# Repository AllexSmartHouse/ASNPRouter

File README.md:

# ASNPRouter
Allex Serial Network Protocol router device based on stm32 board(blue pill) and arduino libs(STM32GENERIC)

# Hardware  
STM32 board - blue pill(or another with simillar pinout)  

DC-DC converter(default PCB based on LM2596)

PCB designed to use with cheap plastic case:  

# Software  
Arduino Libs:  
https://github.com/AllexSmartHouse/STM32GENERIC  

Use ST-Link  
Settings:  
Board: Blue pill  
USB: Disabled, No usb  
Serial communication: SerialUART1  
JTAG/SWD debugging: SWD
Upload method: ST-Link

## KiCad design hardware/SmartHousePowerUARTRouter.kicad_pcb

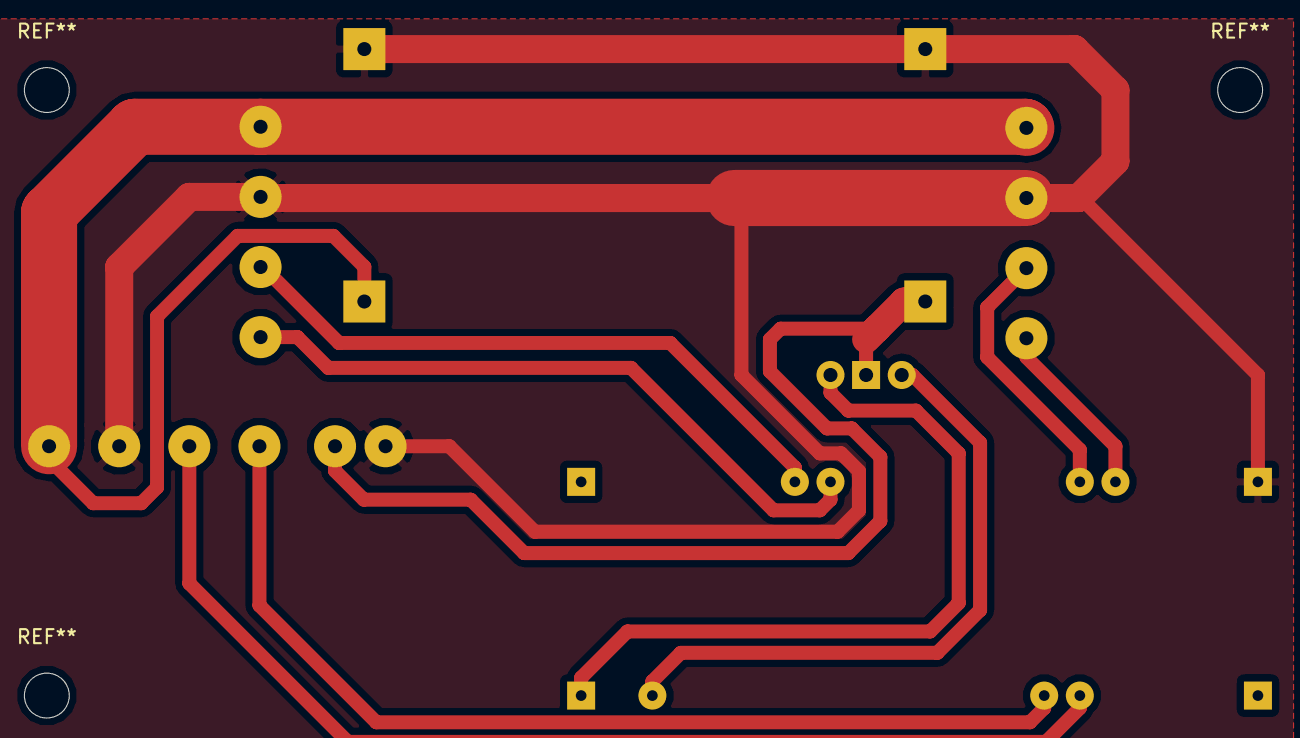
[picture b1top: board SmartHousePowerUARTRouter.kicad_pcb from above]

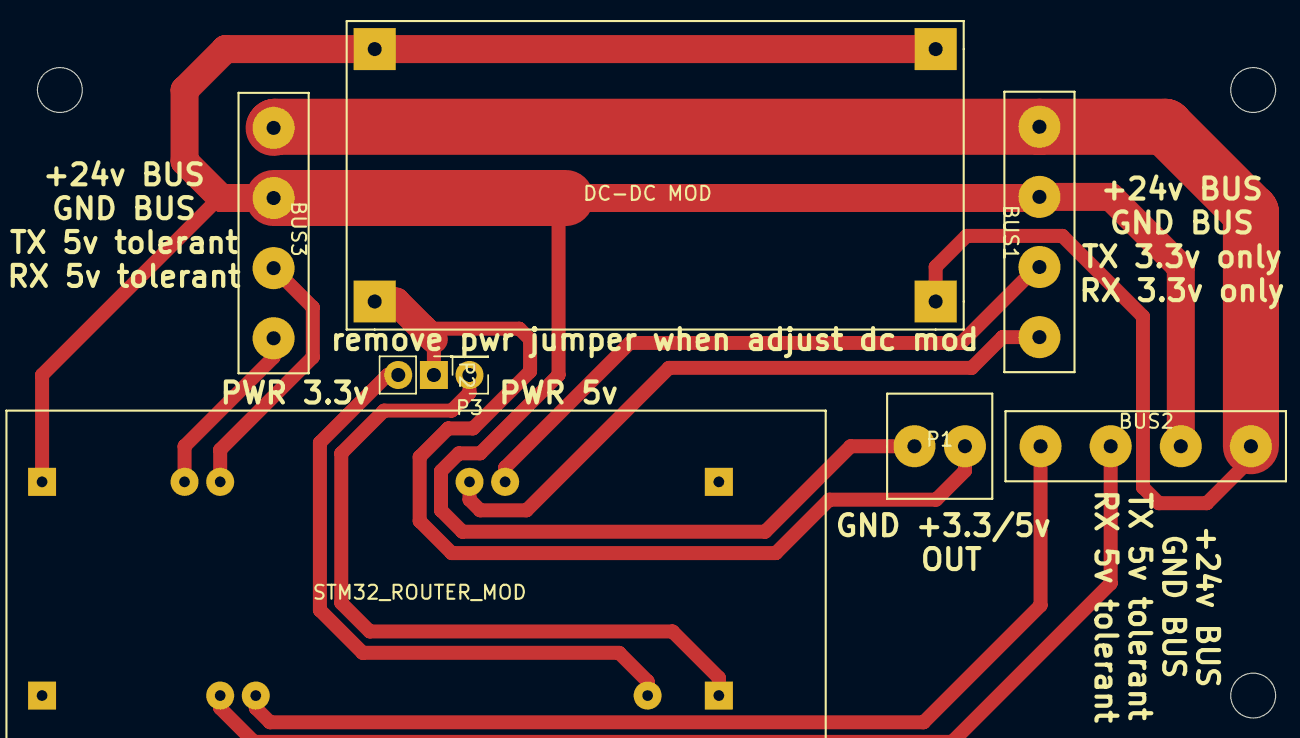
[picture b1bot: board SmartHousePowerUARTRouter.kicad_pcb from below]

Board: 2 copper layers, 8 parts (8 on the bottom side), 11 nets.

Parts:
BUS1, BUS2, BUS3: CONN_01X04; CONN_4_5mm
DC-DC MOD: LM2596_MOD
P1: CONN_01X02; CONN_2_3.5mm
P2: CONN_01X02; Pin_Header_Straight_1x02_Pitch2.54mm
P3: CONN_01X01; Pin_Header_Straight_1x01_Pitch2.54mm
STM32_ROUTER_MOD: STM32DISCOVERY; STM32_DISCOVERY

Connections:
unnamed: BUS1.1, STM32_ROUTER_MOD.28
unnamed: BUS1.2, STM32_ROUTER_MOD.27
unnamed: BUS1.3, BUS2.2, BUS3.2, DC-DC MOD.1, DC-DC MOD.4, P1.2, STM32_ROUTER_MOD.40
unnamed: BUS1.4, BUS2.1, BUS3.1, DC-DC MOD.2
unnamed: BUS2.3, STM32_ROUTER_MOD.15
unnamed: BUS2.4, STM32_ROUTER_MOD.14
unnamed: BUS3.3, STM32_ROUTER_MOD.35
unnamed: BUS3.4, STM32_ROUTER_MOD.36
unnamed: DC-DC MOD.3, P1.1, P2.1
unnamed: P2.2, STM32_ROUTER_MOD.3
unnamed: P3.1, STM32_ROUTER_MOD.1

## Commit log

2017-11-12 -Add kicad project -Add arduino project
2017-12-25 -First release
